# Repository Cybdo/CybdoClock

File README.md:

# CybdoClock!!

14 by 14 letter word clock / calendar / whatever, powered by esp32-c6!

Word clocks are arguably better and cooler than normal analog or digital clocks, but they are way too expensive comercially for a decent product, and even then there's not much customisation to it (the only one i could find was over 1000 dollars and could only show the time in 5 minute increments). CybdoClock was made to be able to show time down to the minute, in multiple formats, all while being customisable and allowing for different uses. The face plate can be swapped to show different languages or formats, and a calendar faceplate is coming soon!

# zine page
pdf at `./zine.pdf`

# Features
- native wifi, bluetooth and matter over thread capabilities
- support for custom faceplates with an easy to update firmware dict
- NTP time sync via wifi
- wall-mountable via command strips
- stand included for desktop use

# Assembly

The housing requires 4x M3 screws, as well as 4x M3 heat-set inserts, and 4x 5mm diameter, 2.5mm thick magnets.
Each faceplate also requires 4x 4x 5mm diameter, 2.5mm thick magnets, in the opposite polarity to the housing.
Magnets should be able to friction fit and stay in place, however a drop of superglue can aid in its placement.

# Usage
- flash circuitpython 10 onto the ESP-32 via USB-C.
- Copy the firmware folder onto the CIRCUITPY drive, and create settings.toml using settings.toml.example.
- install all requirements in requirements.txt using `circup install -r requirements.txt`

CybdoClock will now turn on and sync to NTP once connected to a USB power source!

# Firmware
CybdoClock runs off CircuitPython 10.x, and code can be found under `./firmware/`

# Technical Documentation

CybdoClock is powered by a 14x14 LED matrix. NOTE: CybdoClock refreshes vertically, and defaults to left -> right. This is a hardware limitation, and overrides in firmware could cause permanent damage to components.

## Shift Registers

While the provided firmware uses the adafruit library and pins, a custom firmware can interface with the pins by sending the following serial data:

| 0 | 1 | 2 | 3 | 4 | 5 | 6 | 7 | 8 | 9 | 10 | 11 | 12 | 13 | 14 | 15 | 16 | 17 | 18 | 19 | 20 | 21 | 22 | 23 | 24 | 25 | 26 | 27 | 28 | 29 | 30 | 31 |
|---|---|---|---|---|---|---|---|---|---|---|---|---|---|---|---|---|---|---|---|---|---|---|---|---|---|---|---|---|---|---|---|
| Row 14 | Row 13 | Row 12 | Row 11 | Row 10 | Row 9 | Row 8 | NC | Row 7 | Row 6 | Row 5 | Row 4 | Row 3 | Row 2 | Row 1 | NC | Col 14 | Col 13 | Col 12 | Col 11 | Col 10 | Col 9 | Col 8 | NC | Col 7 | Col 6 | Col 5 | Col 4 | Col 3 | Col 2 | Col 1 | NC |
## Schematics

Please note - the net labels for columns and rows do not reflect their physical layouts, nor does the layout of the matrix in the schematic
a pdf can be found at `./schematics.pdf`

## PCB

# Acknowledgements
 - [KiCad](https://www.kicad.org)
 - [Hack Club Fallout](https://fallout.hackclub.com)
 - [pcb2blender](https://github.com/30350n/pcb2blender)
 - [Blender](https://blender.org)
 - [CircuitPython](https://circuitpython.org/)

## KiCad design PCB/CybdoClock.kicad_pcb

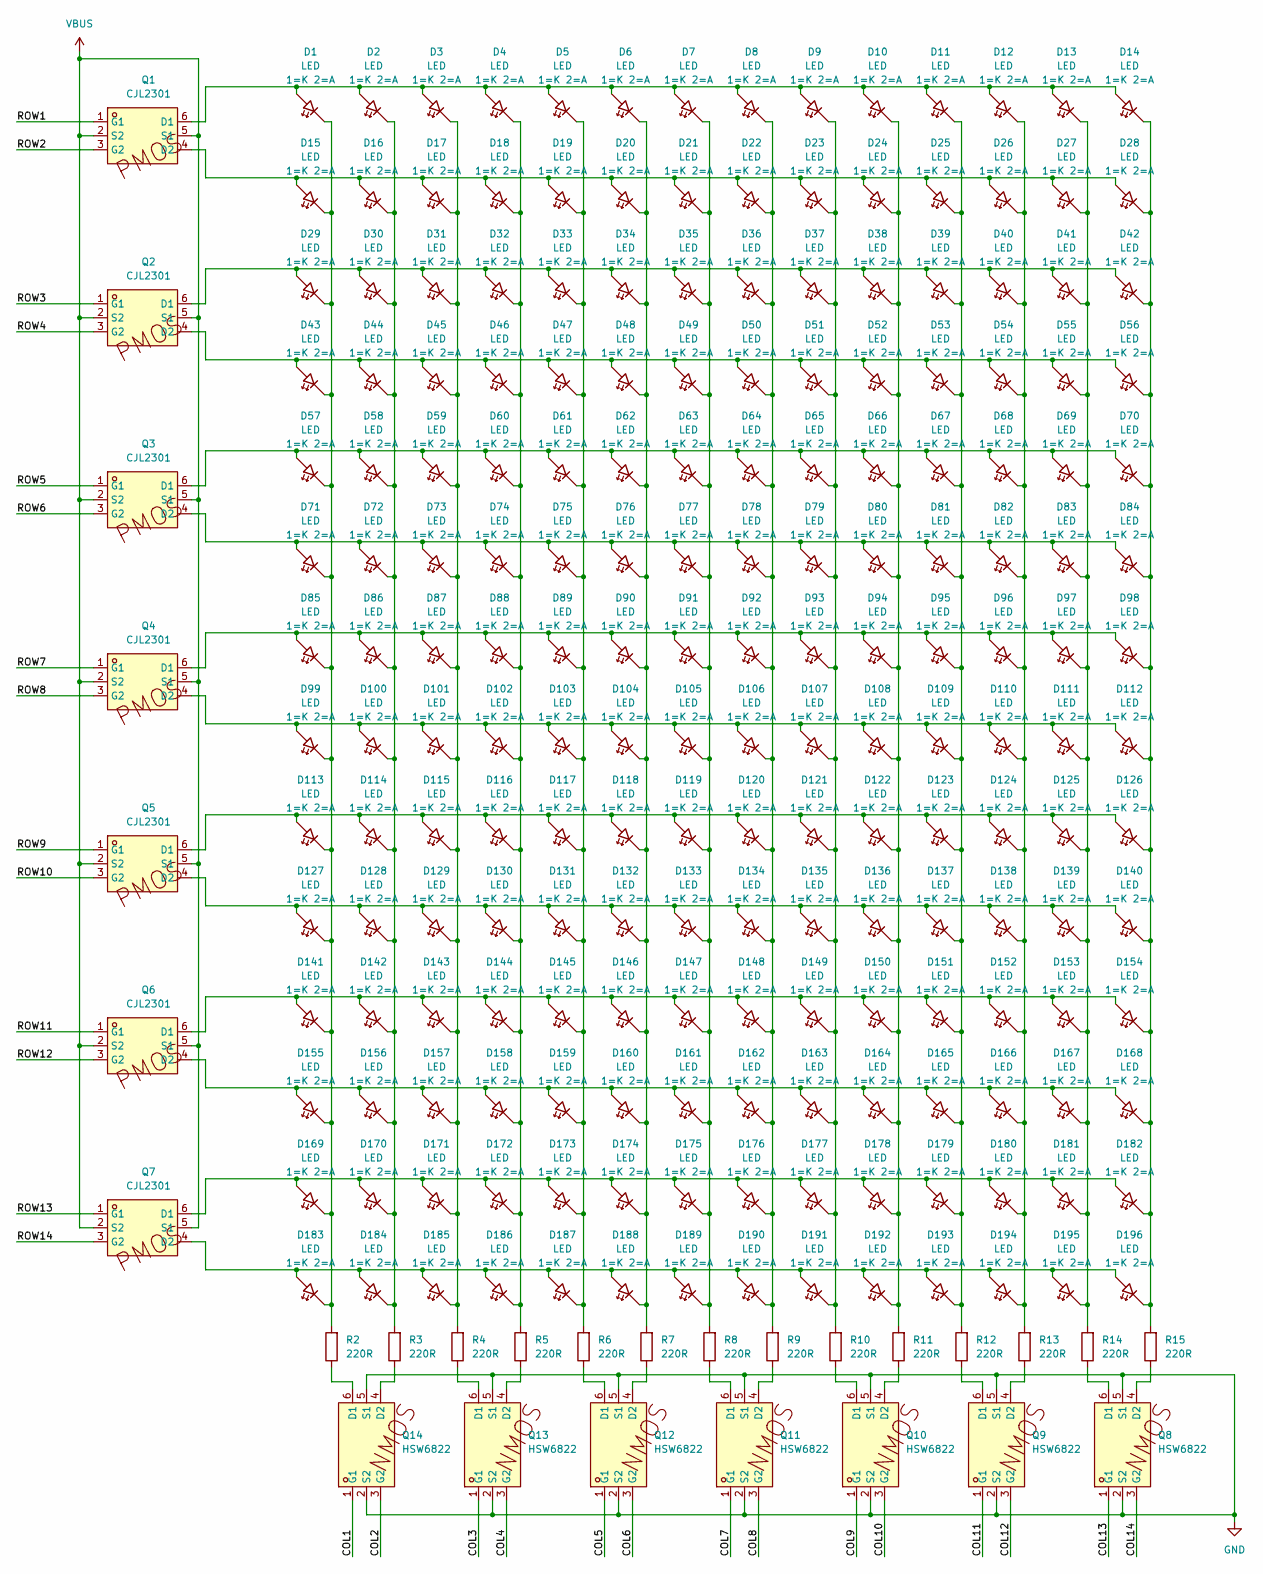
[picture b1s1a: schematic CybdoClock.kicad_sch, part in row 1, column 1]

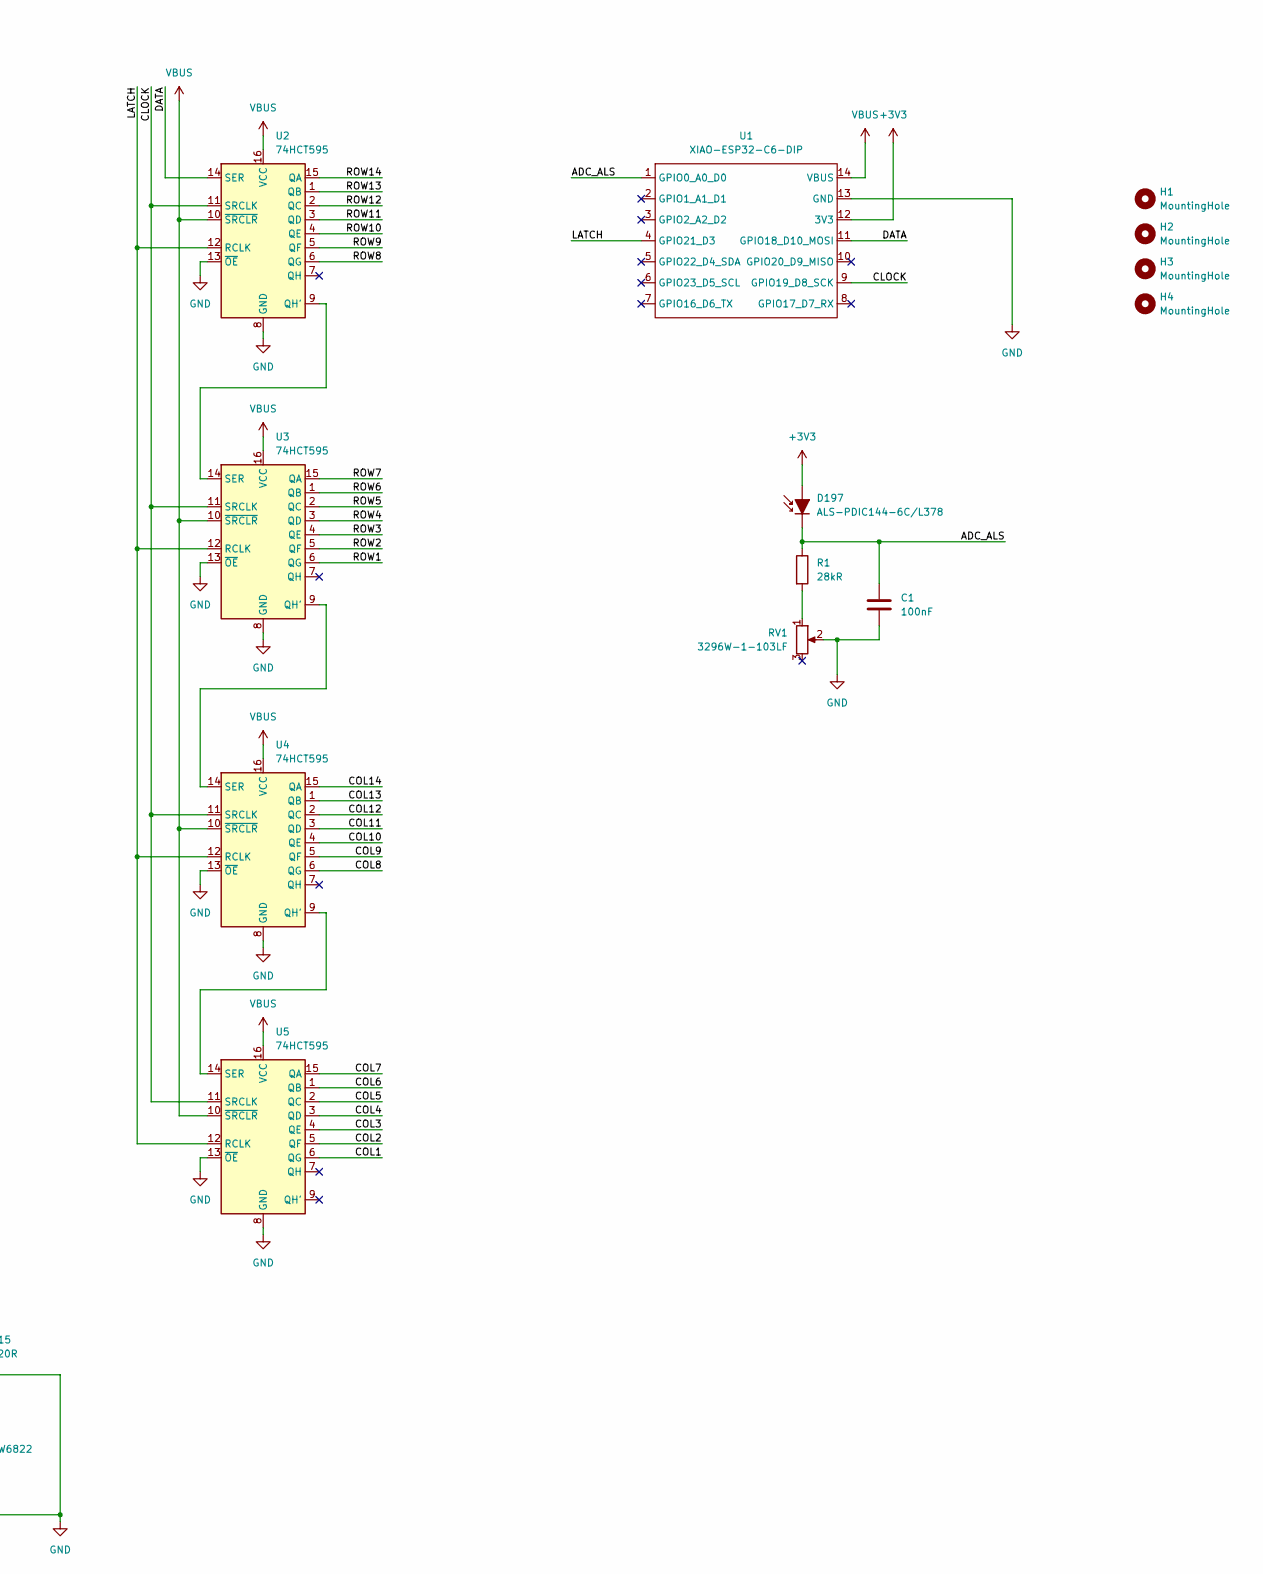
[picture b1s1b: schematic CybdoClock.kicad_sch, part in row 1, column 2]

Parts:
C1: 100nF; C_0402_1005Metric_Pad0.74x0.62mm_HandSolder
D1, D2, D3, D4, D5, D6, D7, D8, D9, D10, D11, D12, D13, D14, D15, D16, D17, D18, D19, D20, D21, D22, D23, D24, D25, D26, D27, D28, D29, D30, D31, D32, D33, D34, D35, D36, D37, D38, D39, D40, D41, D42, D43, D44, D45, D46, D47, D48, D49, D50, D51, D52, D53, D54, D55, D56, D57, D58, D59, D60, D61, D62, D63, D64, D65, D66, D67, D68, D69, D70, D71, D72, D73, D74, D75, D76, D77, D78, D79, D80, D81, D82, D83, D84, D85, D86, D87, D88, D89, D90, D91, D92, D93, D94, D95, D96, D97, D98, D99, D100, D101, D102, D103, D104, D105, D106, D107, D108, D109, D110, D111, D112, D113, D114, D115, D116, D117, D118, D119, D120, D121, D122, D123, D124, D125, D126, D127, D128, D129, D130, D131, D132, D133, D134, D135, D136, D137, D138, D139, D140, D141, D142, D143, D144, D145, D146, D147, D148, D149, D150, D151, D152, D153, D154, D155, D156, D157, D158, D159, D160, D161, D162, D163, D164, D165, D166, D167, D168, D169, D170, D171, D172, D173, D174, D175, D176, D177, D178, D179, D180, D181, D182, D183, D184, D185, D186, D187, D188, D189, D190, D191, D192, D193, D194, D195, D196: LED; LED_D5.0mm
D197: ALS-PDIC144-6C/L378; LED_D3.0mm
H1, H2, H3, H4: MountingHole; MountingHole_3.2mm_M3
Q1, Q2, Q3, Q4, Q5, Q6, Q7: CJL2301; SOT-23-6_L2.9-W1.6-P0.95-LS2.8-BL; MPN CJL2301; LCSC Part C504149
Q8, Q9, Q10, Q11, Q12, Q13, Q14: HSW6822; SOT-23-6_L2.9-W1.6-P0.95-LS2.8-BL; MPN HSW6822; LCSC Part C22359228
R1: 28kR; R_0402_1005Metric_Pad0.72x0.64mm_HandSolder
R2, R3, R4, R5, R6, R7, R8, R9, R10, R11, R12, R13, R14, R15: 220R; R_0402_1005Metric_Pad0.72x0.64mm_HandSolder
RV1: 3296W-1-103LF; Potentiometer_Bourns_3296W_Vertical
U1: XIAO-ESP32-C6-DIP
U2, U3, U4, U5: 74HCT595; SOIC-16_3.9x9.9mm_P1.27mm

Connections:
+3V3: D197.2 (A), U1.12 (3V3)
/ADC_ALS: C1.1, D197.1 (K), R1.1, U1.1 (GPIO0_A0_D0)
/CLOCK: U1.9 (GPIO19_D8_SCK), U2.11 (SRCLK), U3.11 (SRCLK), U4.11 (SRCLK), U5.11 (SRCLK)
/COL1: Q14.1 (G1), U5.6 (QG)
/COL2: Q14.3 (G2), U5.5 (QF)
/COL3: Q13.1 (G1), U5.4 (QE)
/COL4: Q13.3 (G2), U5.3 (QD)
/COL5: Q12.1 (G1), U5.2 (QC)
/COL6: Q12.3 (G2), U5.1 (QB)
/COL7: Q11.1 (G1), U5.15 (QA)
/COL8: Q11.3 (G2), U4.6 (QG)
/COL9: Q10.1 (G1), U4.5 (QF)
/COL10: Q10.3 (G2), U4.4 (QE)
/COL11: Q9.1 (G1), U4.3 (QD)
/COL12: Q9.3 (G2), U4.2 (QC)
/COL13: Q8.1 (G1), U4.1 (QB)
/COL14: Q8.3 (G2), U4.15 (QA)
/DATA: U1.11 (GPIO18_D10_MOSI), U2.14 (SER)
/LATCH: U1.4 (GPIO21_D3), U2.12 (RCLK), U3.12 (RCLK), U4.12 (RCLK), U5.12 (RCLK)
/ROW1: Q1.1 (G1), U3.6 (QG)
/ROW2: Q1.3 (G2), U3.5 (QF)
/ROW3: Q2.1 (G1), U3.4 (QE)
/ROW4: Q2.3 (G2), U3.3 (QD)
/ROW5: Q3.1 (G1), U3.2 (QC)
/ROW6: Q3.3 (G2), U3.1 (QB)
/ROW7: Q4.1 (G1), U3.15 (QA)
/ROW8: Q4.3 (G2), U2.6 (QG)
/ROW9: Q5.1 (G1), U2.5 (QF)
/ROW10: Q5.3 (G2), U2.4 (QE)
/ROW11: Q6.1 (G1), U2.3 (QD)
/ROW12: Q6.3 (G2), U2.2 (QC)
/ROW13: Q7.1 (G1), U2.1 (QB)
/ROW14: Q7.3 (G2), U2.15 (QA)
GND: C1.2, Q8.2 (S2), Q8.5 (S1), Q9.2 (S2), Q9.5 (S1), Q10.2 (S2), Q10.5 (S1), Q11.2 (S2), Q11.5 (S1), Q12.2 (S2), Q12.5 (S1), Q13.2 (S2), Q13.5 (S1), Q14.2 (S2), Q14.5 (S1), RV1.2, U1.13 (GND), U2.8 (GND), U2.13 (~OE), U3.8 (GND), U3.13 (~OE), U4.8 (GND), U4.13 (~OE), U5.8 (GND), U5.13 (~OE)
unnamed: D1.2 (A), D2.2 (A), D3.2 (A), D4.2 (A), D5.2 (A), D6.2 (A), D7.2 (A), D8.2 (A), D9.2 (A), D10.2 (A), D11.2 (A), D12.2 (A), D13.2 (A), D14.2 (A), Q1.6 (D1)
unnamed: D1.1 (K), D15.1 (K), D29.1 (K), D43.1 (K), D57.1 (K), D71.1 (K), D85.1 (K), D99.1 (K), D113.1 (K), D127.1 (K), D141.1 (K), D155.1 (K), D169.1 (K), D183.1 (K), R2.2
unnamed: D10.1 (K), D24.1 (K), D38.1 (K), D52.1 (K), D66.1 (K), D80.1 (K), D94.1 (K), D108.1 (K), D122.1 (K), D136.1 (K), D150.1 (K), D164.1 (K), D178.1 (K), D192.1 (K), R11.2
unnamed: D15.2 (A), D16.2 (A), D17.2 (A), D18.2 (A), D19.2 (A), D20.2 (A), D21.2 (A), D22.2 (A), D23.2 (A), D24.2 (A), D25.2 (A), D26.2 (A), D27.2 (A), D28.2 (A), Q1.4 (D2)
unnamed: D29.2 (A), D30.2 (A), D31.2 (A), D32.2 (A), D33.2 (A), D34.2 (A), D35.2 (A), D36.2 (A), D37.2 (A), D38.2 (A), D39.2 (A), D40.2 (A), D41.2 (A), D42.2 (A), Q2.6 (D1)
unnamed: D43.2 (A), D44.2 (A), D45.2 (A), D46.2 (A), D47.2 (A), D48.2 (A), D49.2 (A), D50.2 (A), D51.2 (A), D52.2 (A), D53.2 (A), D54.2 (A), D55.2 (A), D56.2 (A), Q2.4 (D2)
unnamed: D57.2 (A), D58.2 (A), D59.2 (A), D60.2 (A), D61.2 (A), D62.2 (A), D63.2 (A), D64.2 (A), D65.2 (A), D66.2 (A), D67.2 (A), D68.2 (A), D69.2 (A), D70.2 (A), Q3.6 (D1)
unnamed: D71.2 (A), D72.2 (A), D73.2 (A), D74.2 (A), D75.2 (A), D76.2 (A), D77.2 (A), D78.2 (A), D79.2 (A), D80.2 (A), D81.2 (A), D82.2 (A), D83.2 (A), D84.2 (A), Q3.4 (D2)
unnamed: D85.2 (A), D86.2 (A), D87.2 (A), D88.2 (A), D89.2 (A), D90.2 (A), D91.2 (A), D92.2 (A), D93.2 (A), D94.2 (A), D95.2 (A), D96.2 (A), D97.2 (A), D98.2 (A), Q4.6 (D1)
unnamed: D99.2 (A), D100.2 (A), D101.2 (A), D102.2 (A), D103.2 (A), D104.2 (A), D105.2 (A), D106.2 (A), D107.2 (A), D108.2 (A), D109.2 (A), D110.2 (A), D111.2 (A), D112.2 (A), Q4.4 (D2)
unnamed: D2.1 (K), D16.1 (K), D30.1 (K), D44.1 (K), D58.1 (K), D72.1 (K), D86.1 (K), D100.1 (K), D114.1 (K), D128.1 (K), D142.1 (K), D156.1 (K), D170.1 (K), D184.1 (K), R3.2
unnamed: D3.1 (K), D17.1 (K), D31.1 (K), D45.1 (K), D59.1 (K), D73.1 (K), D87.1 (K), D101.1 (K), D115.1 (K), D129.1 (K), D143.1 (K), D157.1 (K), D171.1 (K), D185.1 (K), R4.2
unnamed: D4.1 (K), D18.1 (K), D32.1 (K), D46.1 (K), D60.1 (K), D74.1 (K), D88.1 (K), D102.1 (K), D116.1 (K), D130.1 (K), D144.1 (K), D158.1 (K), D172.1 (K), D186.1 (K), R5.2
unnamed: D5.1 (K), D19.1 (K), D33.1 (K), D47.1 (K), D61.1 (K), D75.1 (K), D89.1 (K), D103.1 (K), D117.1 (K), D131.1 (K), D145.1 (K), D159.1 (K), D173.1 (K), D187.1 (K), R6.2
unnamed: D6.1 (K), D20.1 (K), D34.1 (K), D48.1 (K), D62.1 (K), D76.1 (K), D90.1 (K), D104.1 (K), D118.1 (K), D132.1 (K), D146.1 (K), D160.1 (K), D174.1 (K), D188.1 (K), R7.2
unnamed: D7.1 (K), D21.1 (K), D35.1 (K), D49.1 (K), D63.1 (K), D77.1 (K), D91.1 (K), D105.1 (K), D119.1 (K), D133.1 (K), D147.1 (K), D161.1 (K), D175.1 (K), D189.1 (K), R8.2
unnamed: D8.1 (K), D22.1 (K), D36.1 (K), D50.1 (K), D64.1 (K), D78.1 (K), D92.1 (K), D106.1 (K), D120.1 (K), D134.1 (K), D148.1 (K), D162.1 (K), D176.1 (K), D190.1 (K), R9.2
unnamed: D9.1 (K), D23.1 (K), D37.1 (K), D51.1 (K), D65.1 (K), D79.1 (K), D93.1 (K), D107.1 (K), D121.1 (K), D135.1 (K), D149.1 (K), D163.1 (K), D177.1 (K), D191.1 (K), R10.2
unnamed: D11.1 (K), D25.1 (K), D39.1 (K), D53.1 (K), D67.1 (K), D81.1 (K), D95.1 (K), D109.1 (K), D123.1 (K), D137.1 (K), D151.1 (K), D165.1 (K), D179.1 (K), D193.1 (K), R12.2
unnamed: D12.1 (K), D26.1 (K), D40.1 (K), D54.1 (K), D68.1 (K), D82.1 (K), D96.1 (K), D110.1 (K), D124.1 (K), D138.1 (K), D152.1 (K), D166.1 (K), D180.1 (K), D194.1 (K), R13.2
unnamed: D13.1 (K), D27.1 (K), D41.1 (K), D55.1 (K), D69.1 (K), D83.1 (K), D97.1 (K), D111.1 (K), D125.1 (K), D139.1 (K), D153.1 (K), D167.1 (K), D181.1 (K), D195.1 (K), R14.2
unnamed: D14.1 (K), D28.1 (K), D42.1 (K), D56.1 (K), D70.1 (K), D84.1 (K), D98.1 (K), D112.1 (K), D126.1 (K), D140.1 (K), D154.1 (K), D168.1 (K), D182.1 (K), D196.1 (K), R15.2
unnamed: D113.2 (A), D114.2 (A), D115.2 (A), D116.2 (A), D117.2 (A), D118.2 (A), D119.2 (A), D120.2 (A), D121.2 (A), D122.2 (A), D123.2 (A), D124.2 (A), D125.2 (A), D126.2 (A), Q5.6 (D1)
unnamed: D127.2 (A), D128.2 (A), D129.2 (A), D130.2 (A), D131.2 (A), D132.2 (A), D133.2 (A), D134.2 (A), D135.2 (A), D136.2 (A), D137.2 (A), D138.2 (A), D139.2 (A), D140.2 (A), Q5.4 (D2)
unnamed: D141.2 (A), D142.2 (A), D143.2 (A), D144.2 (A), D145.2 (A), D146.2 (A), D147.2 (A), D148.2 (A), D149.2 (A), D150.2 (A), D151.2 (A), D152.2 (A), D153.2 (A), D154.2 (A), Q6.6 (D1)
unnamed: D155.2 (A), D156.2 (A), D157.2 (A), D158.2 (A), D159.2 (A), D160.2 (A), D161.2 (A), D162.2 (A), D163.2 (A), D164.2 (A), D165.2 (A), D166.2 (A), D167.2 (A), D168.2 (A), Q6.4 (D2)
unnamed: D169.2 (A), D170.2 (A), D171.2 (A), D172.2 (A), D173.2 (A), D174.2 (A), D175.2 (A), D176.2 (A), D177.2 (A), D178.2 (A), D179.2 (A), D180.2 (A), D181.2 (A), D182.2 (A), Q7.6 (D1)
unnamed: D183.2 (A), D184.2 (A), D185.2 (A), D186.2 (A), D187.2 (A), D188.2 (A), D189.2 (A), D190.2 (A), D191.2 (A), D192.2 (A), D193.2 (A), D194.2 (A), D195.2 (A), D196.2 (A), Q7.4 (D2)
unnamed: Q8.6 (D1), R14.1
unnamed: Q8.4 (D2), R15.1
unnamed: Q9.6 (D1), R12.1
unnamed: Q9.4 (D2), R13.1
unnamed: Q10.6 (D1), R10.1
unnamed: Q10.4 (D2), R11.1
unnamed: Q11.6 (D1), R8.1
unnamed: Q11.4 (D2), R9.1
unnamed: Q12.6 (D1), R6.1
unnamed: Q12.4 (D2), R7.1
unnamed: Q13.6 (D1), R4.1
unnamed: Q13.4 (D2), R5.1
unnamed: Q14.6 (D1), R2.1
unnamed: Q14.4 (D2), R3.1
unnamed: R1.2, RV1.1
unnamed: U2.9 (QH'), U3.14 (SER)
unnamed: U3.9 (QH'), U4.14 (SER)
unnamed: U4.9 (QH'), U5.14 (SER)
VBUS: Q1.2 (S2), Q1.5 (S1), Q2.2 (S2), Q2.5 (S1), Q3.2 (S2), Q3.5 (S1), Q4.2 (S2), Q4.5 (S1), Q5.2 (S2), Q5.5 (S1), Q6.2 (S2), Q6.5 (S1), Q7.2 (S2), Q7.5 (S1), U1.14 (VBUS), U2.10 (~SRCLR), U2.16 (VCC), U3.10 (~SRCLR), U3.16 (VCC), U4.10 (~SRCLR), U4.16 (VCC), U5.10 (~SRCLR), U5.16 (VCC)

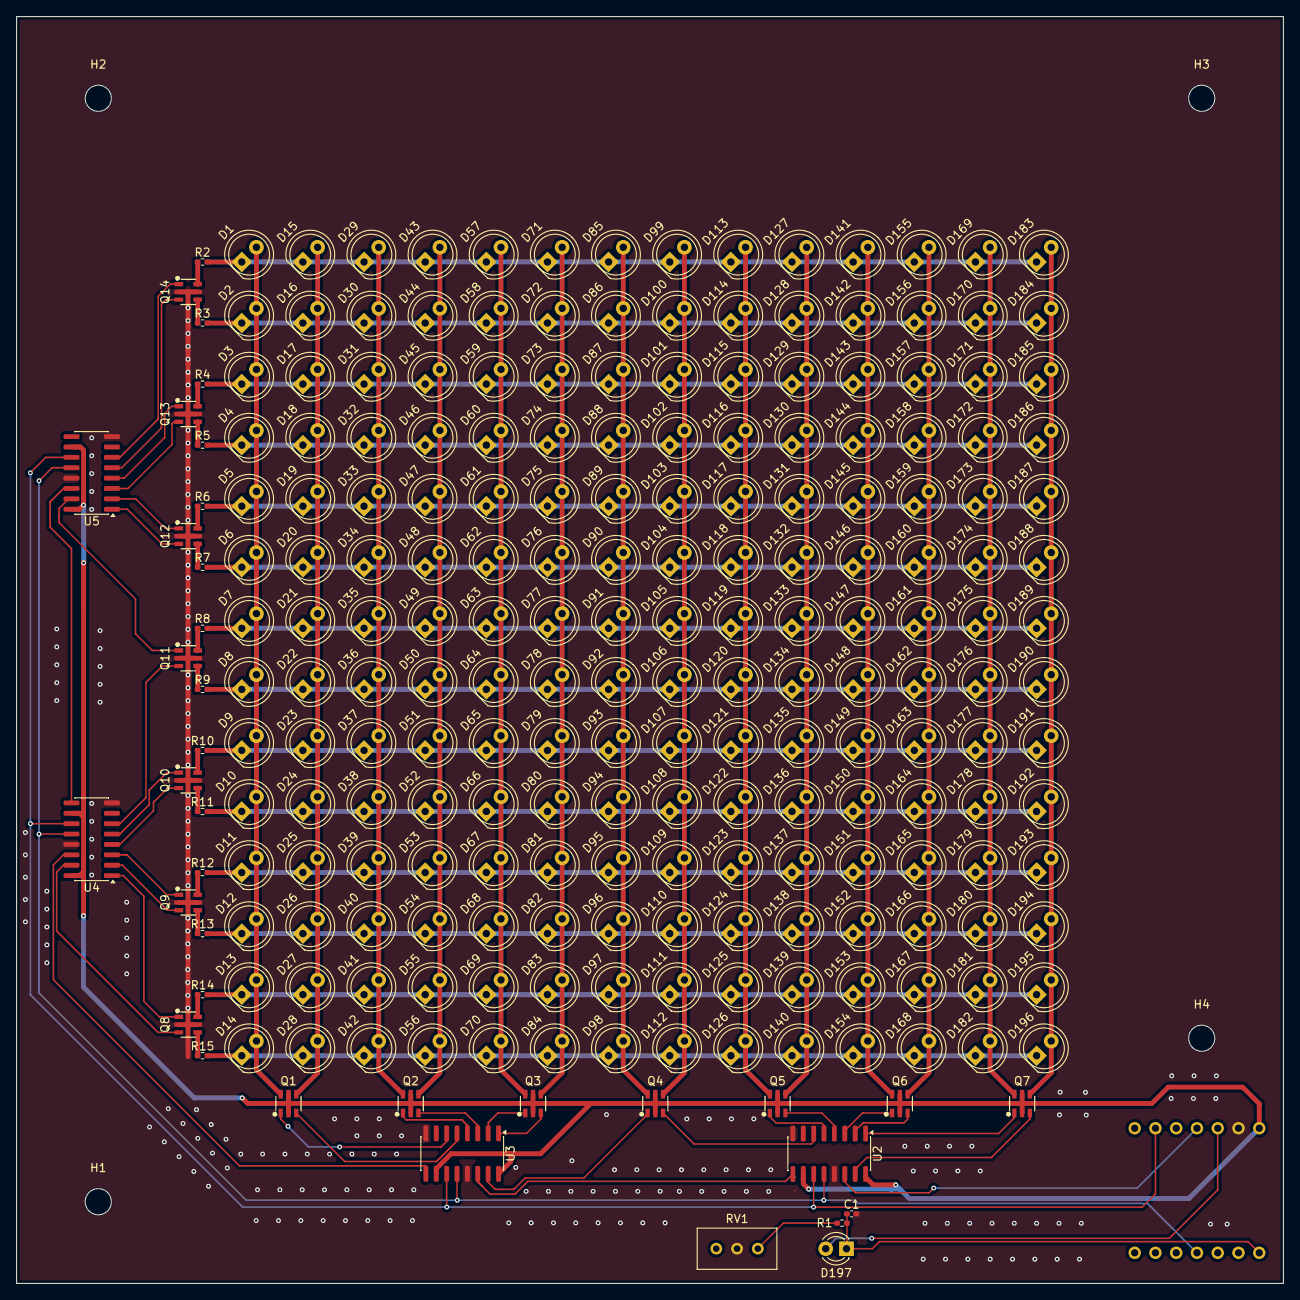
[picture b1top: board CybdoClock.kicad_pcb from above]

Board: 2 copper layers, 155.0 x 155.0 mm, 237 parts (1 on the bottom side), 81 nets.

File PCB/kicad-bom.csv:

"Id","Designator","Footprint","Quantity","Designation","Supplier and ref",
1,"C1","C_0402_1005Metric_Pad0.74x0.62mm_HandSolder",1,"100nF",,,
2,"D1, D2, D3, D4, D5, D6, D7, D8, D9, D10, D11, D12, D13, D14, D15, D16, D17, D18, D19, D20, D21, D22, D23, D24, D25, D26, D27, D28, D29, D30, D31, D32, D33, D34, D35, D36, D37, D38, D39, D40, D41, D42, D43, D44, D45, D46, D47, D48, D49, D50, D51, D52, D53, D54, D55, D56, D57, D58, D59, D60, D61, D62, D63, D64, D65, D66, D67, D68, D69, D70, D71, D72, D73, D74, D75, D76, D77, D78, D79, D80, D81, D82, D83, D84, D85, D86, D87, D88, D89, D90, D91, D92, D93, D94, D95, D96, D97, D98, D99, D100, D101, D102, D103, D104, D105, D106, D107, D108, D109, D110, D111, D112, D113, D114, D115, D116, D117, D118, D119, D120, D121, D122, D123, D124, D125, D126, D127, D128, D129, D130, D131, D132, D133, D134, D135, D136, D137, D138, D139, D140, D141, D142, D143, D144, D145, D146, D147, D148, D149, D150, D151, D152, D153, D154, D155, D156, D157, D158, D159, D160, D161, D162, D163, D164, D165, D166, D167, D168, D169, D170, D171, D172, D173, D174, D175, D176, D177, D178, D179, D180, D181, D182, D183, D184, D185, D186, D187, D188, D189, D190, D191, D192, D193, D194, D195, D196","LED_D5.0mm",196,"LED",,,
3,"D197","LED_D3.0mm",1,"ALS-PDIC144-6C/L378",,,
4,"Q1, Q2, Q3, Q4, Q5, Q6, Q7","SOT-23-6_L2.9-W1.6-P0.95-LS2.8-BL",7,"CJL2301",,,
5,"Q8, Q9, Q10, Q11, Q12, Q13, Q14","SOT-23-6_L2.9-W1.6-P0.95-LS2.8-BL",7,"HSW6822",,,
6,"R1","R_0402_1005Metric_Pad0.72x0.64mm_HandSolder",1,"28kR",,,
7,"R2, R3, R4, R5, R6, R7, R8, R9, R10, R11, R12, R13, R14, R15","R_0402_1005Metric_Pad0.72x0.64mm_HandSolder",14,"220R",,,
8,"RV1","Potentiometer_Bourns_3296W_Vertical",1,"3296W-1-103LF",,,
9,"U1","XIAO-ESP32-C6-DIP",1,"XIAO-ESP32-C6-DIP",,,
10,"U2, U3, U4, U5","SOIC-16_3.9x9.9mm_P1.27mm",4,"74HCT595",,,

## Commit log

2026-06-15 finished the pcb
2026-06-16 updated mounting holes and some 3d models
2026-06-17 use built in serial pins, start on firmware using circuitpython
2026-06-18 firmware done, centered leds positioning
2026-06-19 added 3d models, renders, bom, finalised firmware, pcb
2026-06-19 tidy
2026-06-19 redo the timer
2026-06-19 add esp32 to bom
2026-06-24 bom total
2026-06-24 forgor a comma
